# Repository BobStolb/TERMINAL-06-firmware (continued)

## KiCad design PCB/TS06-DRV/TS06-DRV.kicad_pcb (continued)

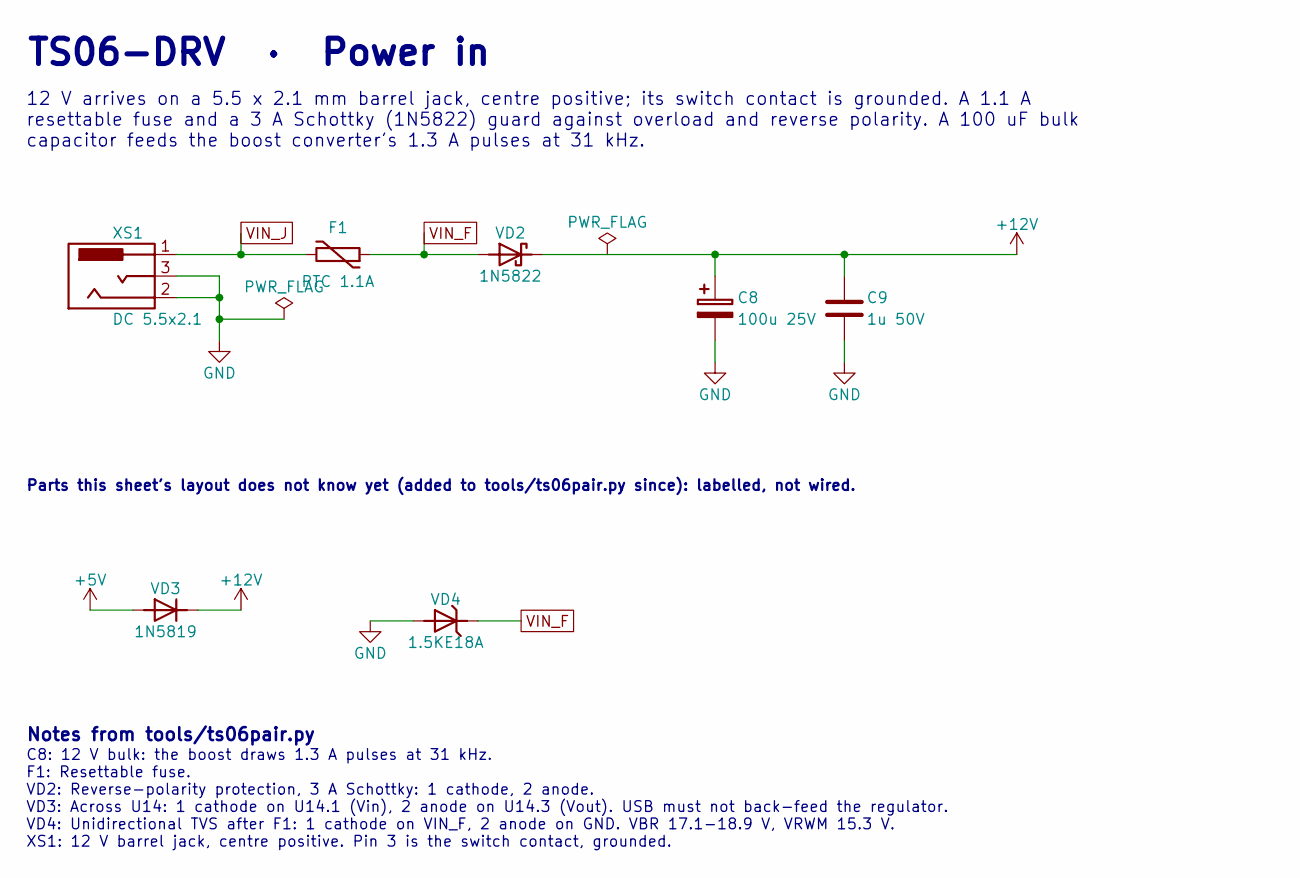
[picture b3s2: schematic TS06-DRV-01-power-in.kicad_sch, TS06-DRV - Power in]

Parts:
C8: 100u 25V; TS06_CP_Radial_D6.3mm_P2.50mm
C9: 1u 50V; TS06_C_Disc_P5.00mm_R270
F1: PTC 1.1A; TS06_Fuse_PTC_MF-RG1100
VD2: 1N5822; TS06_D_DO-201AD_P15.24mm_R180
VD3: 1N5819; TS06_D_DO-41_P10.16mm
VD4: 1.5KE18A; TS06_D_DO-201AD_P15.24mm
XS1: DC 5.5x2.1; TS06_BarrelJack_Horizontal

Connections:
+5V: VD3.2 (A); also elsewhere on the board
+12V: C8.1, C9.1, VD2.1 (K), VD3.1 (K); also elsewhere on the board
GND: C8.2, C9.2, VD4.2 (A), XS1.2 (-), XS1.3 (SW); also elsewhere on the board
VIN_F: F1.2, VD2.2 (A), VD4.1 (K)
VIN_J: F1.1, XS1.1 (+)

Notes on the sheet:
TS06-DRV · Power in
12 V arrives on a 5.5 x 2.1 mm barrel jack, centre positive; its switch contact is grounded. A 1.1 A resettable fuse and a 3 A Schottky (1N5822) guard against overload and reverse polarity. A 100 uF bulk capacitor feeds the boost converter's 1.3 A pulses at 31 kHz.
Parts this sheet's layout does not know yet (added to tools/ts06pair.py since): labelled, not wired.
Notes from tools/ts06pair.py
C8: 12 V bulk: the boost draws 1.3 A pulses at 31 kHz. F1: Resettable fuse. VD2: Reverse-polarity protection, 3 A Schottky: 1 cathode, 2 anode. VD3: Across U14: 1 cathode on U14.1 (Vin), 2 anode on U14.3 (Vout). USB must not back-feed the regulator. VD4: Unidirectional TVS after F1: 1 cathode on VI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

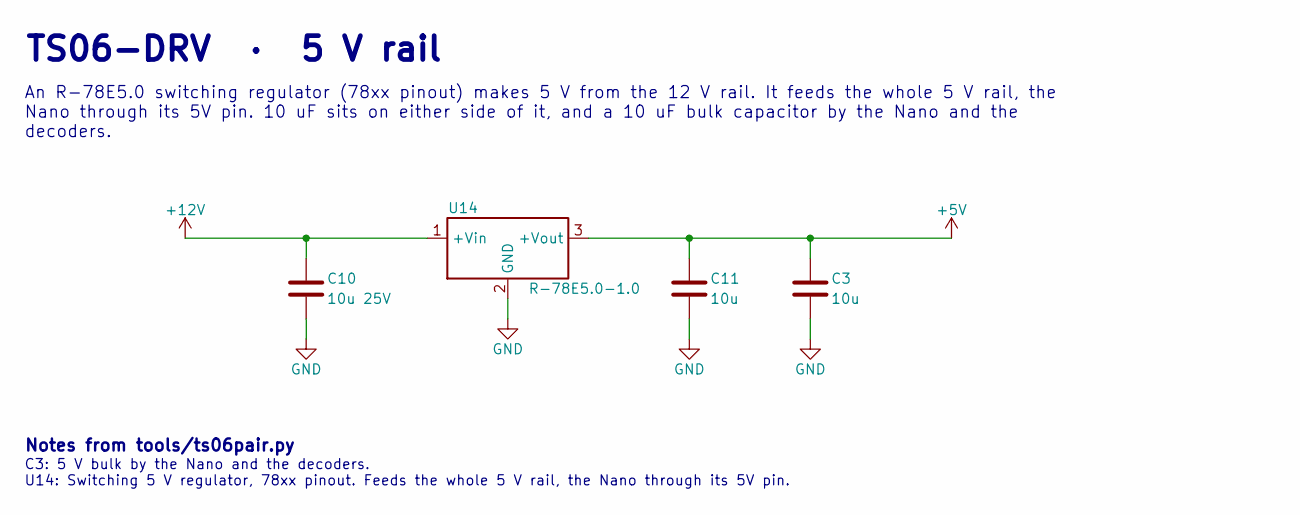
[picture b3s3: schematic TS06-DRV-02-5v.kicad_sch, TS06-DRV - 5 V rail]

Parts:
C3: 10u; TS06_C_Disc_P5.00mm
C10: 10u 25V; TS06_C_Disc_P5.00mm_R270
C11: 10u; TS06_C_Disc_P5.00mm_R90
U14: R-78E5.0-1.0; TS06_R-78E_SIP3

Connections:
+5V: C3.1, C11.1, U14.3 (+Vout); also elsewhere on the board
+12V: C10.1, U14.1 (+Vin); also elsewhere on the board
GND: C3.2, C10.2, C11.2, U14.2 (GND); also elsewhere on the board

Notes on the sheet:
TS06-DRV · 5 V rail
An R-78E5.0 switching regulator (78xx pinout) makes 5 V from the 12 V rail. It feeds the whole 5 V rail, the Nano through its 5V pin. 10 uF sits on either side of it, and a 10 uF bulk capacitor by the Nano and the decoders.
Notes from tools/ts06pair.py
C3: 5 V bulk by the Nano and the decoders. U14: Switching 5 V regulator, 78xx pinout. Feeds the whole 5 V rail, the Nano through its 5V pin.

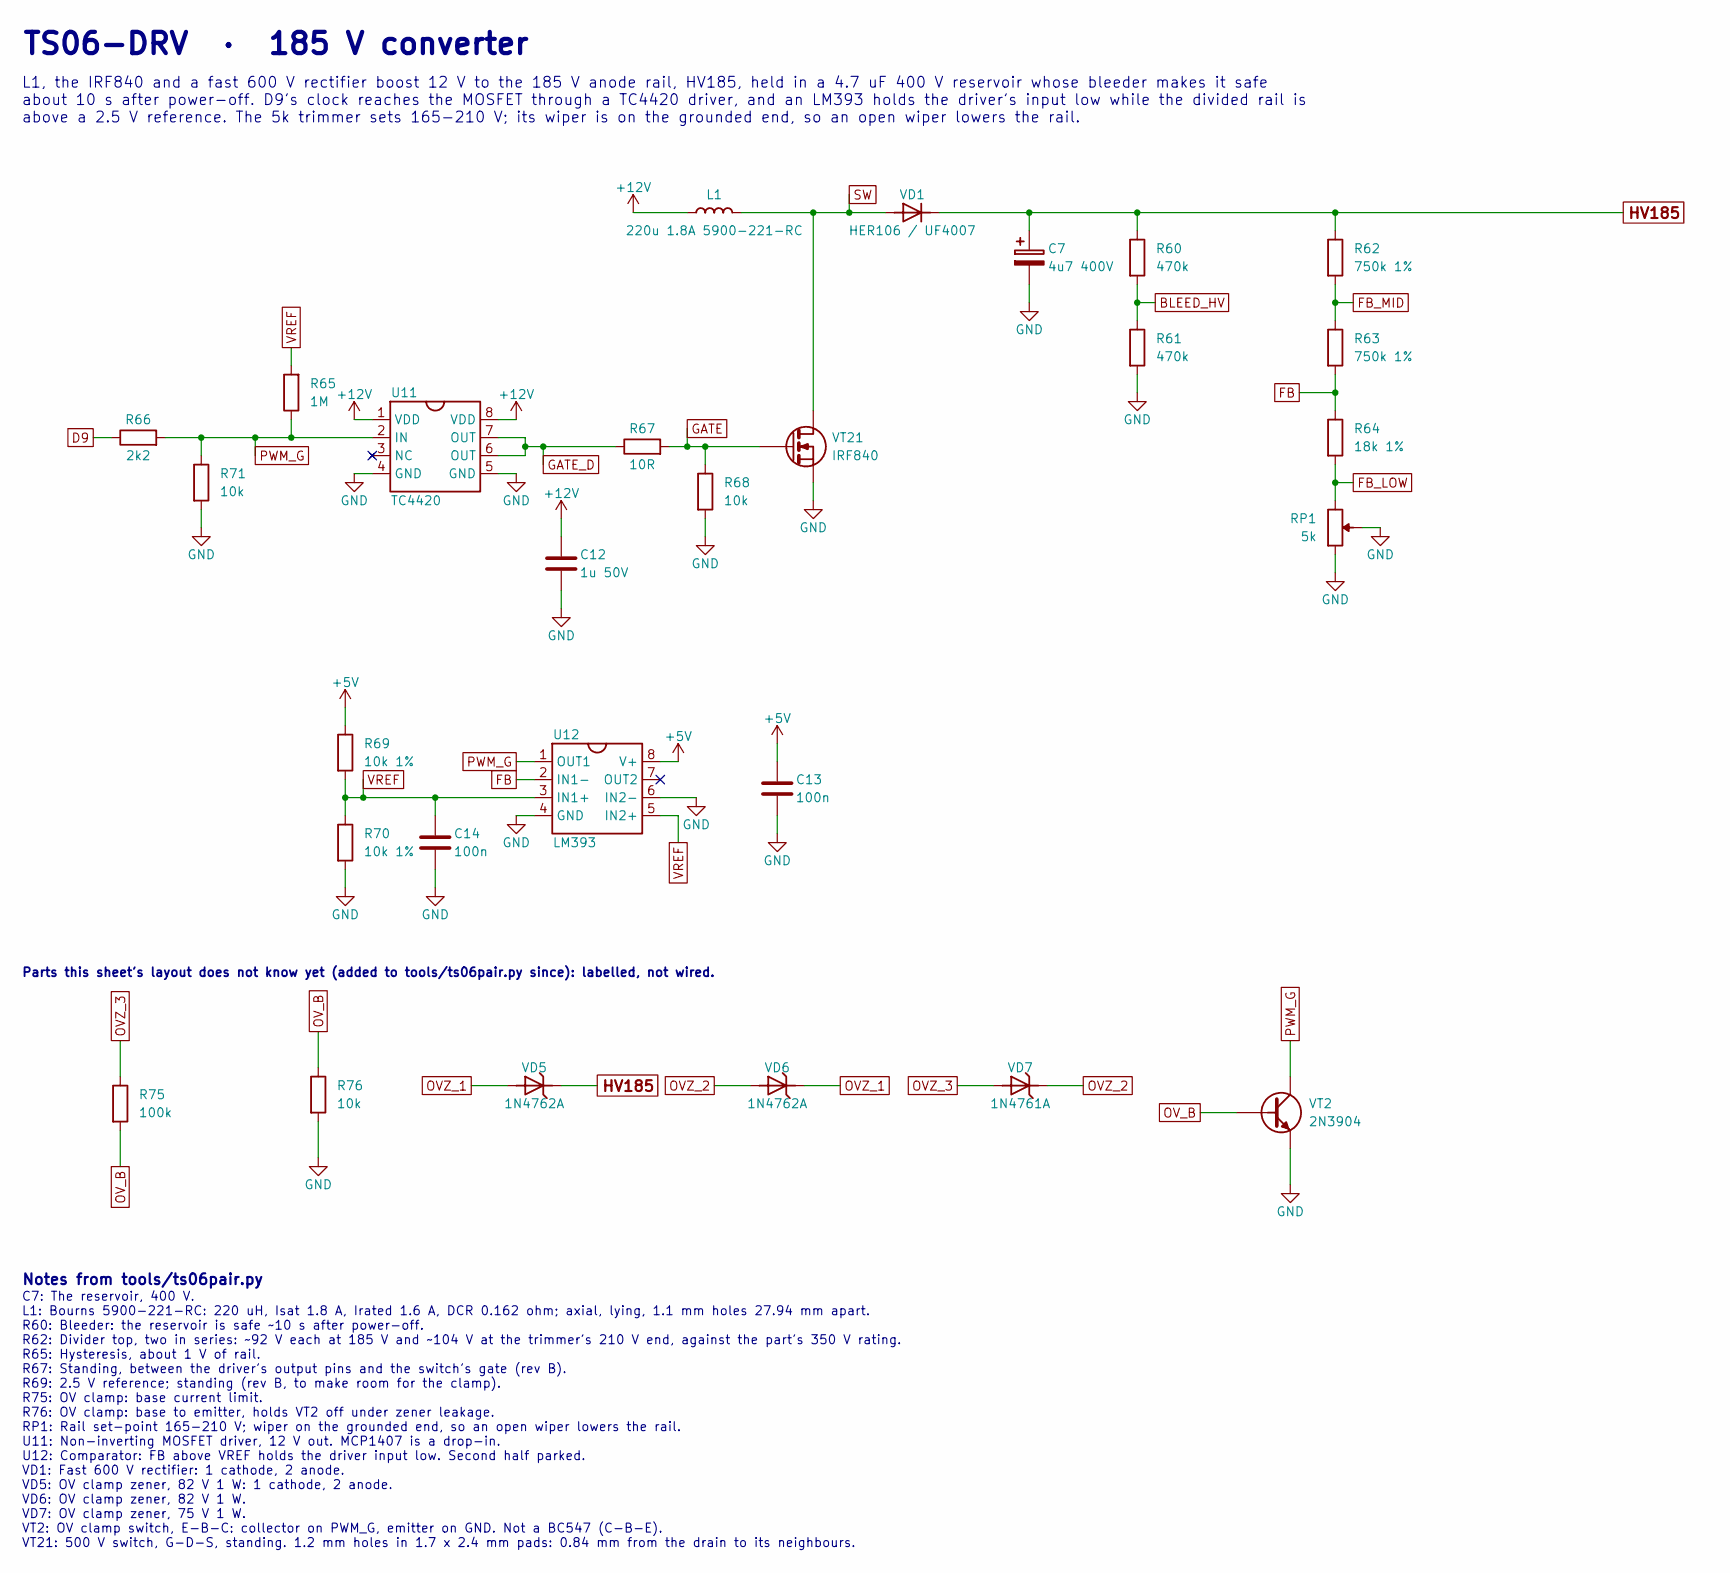
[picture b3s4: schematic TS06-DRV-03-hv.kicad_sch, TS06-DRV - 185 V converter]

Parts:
C7: 4u7 400V; TS06_CP_Radial_D10.0mm_P5.00mm_R180
C12: 1u 50V; TS06_C_Disc_P5.00mm_R270
C13: 100n; TS06_C_Disc_P5.00mm_R180
C14: 100n; TS06_C_Disc_P5.00mm
L1: 220u 1.8A 5900-221-RC; TS06_L_Axial_D11.5mm_L22.9mm_P27.94mm
R60, R61: 470k; TS06_R_Axial_MLT-0.5_P15.24mm
R62: 750k 1%; TS06_R_Axial_MLT-0.5_P15.24mm
R63: 750k 1%; TS06_R_Axial_MLT-0.5_P15.24mm_R270
R64: 18k 1%; TS06_R_Axial_DIN0207_P10.16mm
R65: 1M; TS06_R_Axial_DIN0207_P2.54mm_Vertical_R180
R66: 2k2; TS06_R_Axial_DIN0207_P2.54mm_Vertical_R270
R67: 10R; TS06_R_Axial_DIN0207_P2.54mm_Vertical
R68: 10k; TS06_R_Axial_DIN0207_P2.54mm_Vertical_R90
R69, R70: 10k 1%; TS06_R_Axial_DIN0207_P2.54mm_Vertical_R90
R71: 10k; TS06_R_Axial_DIN0207_P2.54mm_Vertical_R180
R75: 100k; TS06_R_Axial_DIN0207_P10.16mm_R180
R76: 10k; TS06_R_Axial_DIN0207_P10.16mm
RP1: 5k; TS06_Trimmer_3296W
U11: TC4420; TS06_DIP-8_W7.62mm_Socket
U12: LM393; TS06_DIP-8_W7.62mm_Socket_R180
VD1: HER106 / UF4007; TS06_D_DO-41_P10.16mm_R180
VD5: 1N4762A; TS06_D_DO-41_P10.16mm
VD6: 1N4762A; TS06_D_DO-41_P10.16mm_R180
VD7: 1N4761A; TS06_D_DO-41_P10.16mm
VT2: 2N3904; TS06_TO-92_Inline_Wide_R180
VT21: IRF840; TS06_TO-220-3_Vertical_HV

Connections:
+5V: C13.1, R69.1, U12.8 (V+); also elsewhere on the board
+12V: C12.1, L1.1, U11.1 (VDD), U11.8 (VDD); also elsewhere on the board
BLEED_HV: R60.2, R61.1
D9: R66.1; also elsewhere on the board
FB: R63.2, R64.1, U12.2 (IN1-)
FB_LOW: R64.2, RP1.1
FB_MID: R62.2, R63.1
GATE: R67.2, R68.1, VT21.1 (G)
GATE_D: R67.1, U11.6 (OUT), U11.7 (OUT)
GND: C7.2, C12.2, C13.2, C14.2, R61.2, R68.2, R70.2, R71.2, R76.2, RP1.2 (W), RP1.3, U11.4 (GND), U11.5 (GND), U12.4 (GND), U12.6 (IN2-), VT2.1 (E), VT21.3 (S); also elsewhere on the board
HV185: C7.1, R60.1, R62.1, VD1.1 (K), VD5.1 (K); also elsewhere on the board
OVZ_1: VD5.2 (A), VD6.1 (K)
OVZ_2: VD6.2 (A), VD7.1 (K)
OVZ_3: R75.1, VD7.2 (A)
OV_B: R75.2, R76.1, VT2.2 (B)
PWM_G: R65.1, R66.2, R71.1, U11.2 (IN), U12.1 (OUT1), VT2.3 (C)
SW: L1.2, VD1.2 (A), VT21.2 (D)
VREF: C14.1, R65.2, R69.2, R70.1, U12.3 (IN1+), U12.5 (IN2+)

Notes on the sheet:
TS06-DRV · 185 V converter
L1, the IRF840 and a fast 600 V rectifier boost 12 V to the 185 V anode rail, HV185, held in a 4.7 uF 400 V reservoir whose bleeder makes it safe about 10 s after power-off. D9's clock reaches the MOSFET through a TC4420 driver, and an LM393 holds the driver's input low while the divided rail is ab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
Parts this sheet's layout does not know yet (added to tools/ts06pair.py since): labelled, not wired.
Notes from tools/ts06pair.py
C7: The reservoir, 400 V. L1: Bourns 5900-221-RC: 220 uH, Isat 1.8 A, Irated 1.6 A, DCR 0.162 ohm; axial, lying, 1.1 mm holes 27.94 mm apart. R60: Bleeder: the reservoir is safe ~10 s after power-off. R62: Divider top, two in series: ~92 V each at 185 V and ~104 V at the trimmer's 210 V end, agains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

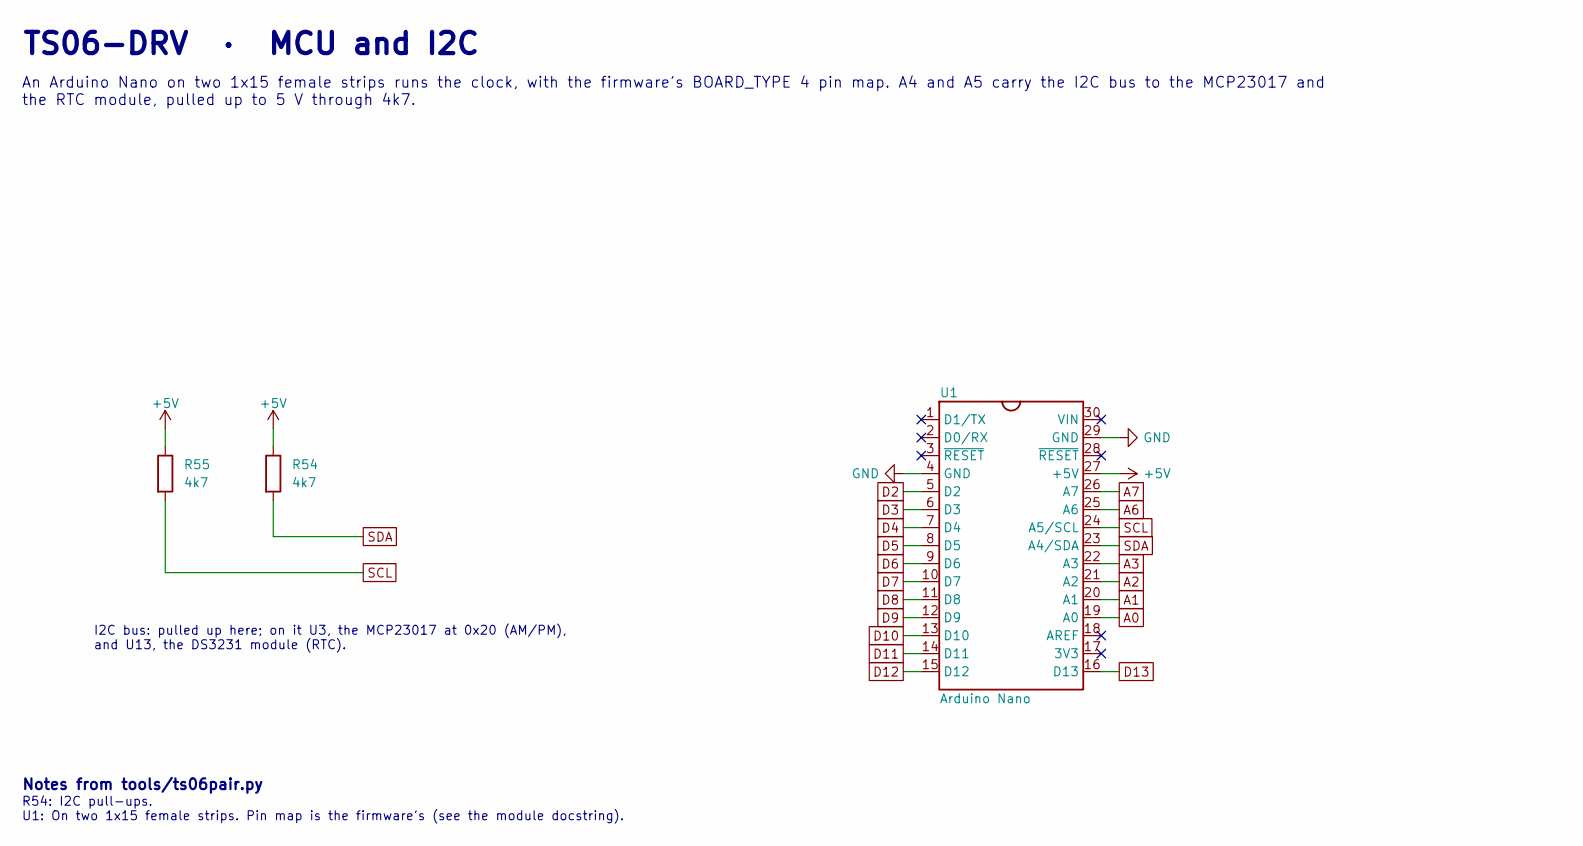
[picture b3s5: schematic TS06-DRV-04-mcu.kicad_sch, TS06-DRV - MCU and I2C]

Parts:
R54, R55: 4k7; TS06_R_Axial_DIN0207_P2.54mm_Vertical
U1: Arduino Nano; TS06_Arduino_Nano_R90

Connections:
+5V: R54.1, R55.1, U1.27 (+5V); also elsewhere on the board
A0: U1.19 (A0); also elsewhere on the board
A1: U1.20 (A1); also elsewhere on the board
A2: U1.21 (A2); also elsewhere on the board
A3: U1.22 (A3); also elsewhere on the board
A6: U1.25 (A6); also elsewhere on the board
A7: U1.26 (A7); also elsewhere on the board
D2: U1.5 (D2); also elsewhere on the board
D3: U1.6 (D3); also elsewhere on the board
D4: U1.7 (D4); also elsewhere on the board
D5: U1.8 (D5); also elsewhere on the board
D6: U1.9 (D6); also elsewhere on the board
D7: U1.10 (D7); also elsewhere on the board
D8: U1.11 (D8); also elsewhere on the board
D9: U1.12 (D9); also elsewhere on the board
D10: U1.13 (D10); also elsewhere on the board
D11: U1.14 (D11); also elsewhere on the board
D12: U1.15 (D12); also elsewhere on the board
D13: U1.16 (D13); also elsewhere on the board
GND: U1.4 (GND), U1.29 (GND); also elsewhere on the board
SCL: R55.2, U1.24 (A5/SCL); also elsewhere on the board
SDA: R54.2, U1.23 (A4/SDA); also elsewhere on the board

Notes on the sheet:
TS06-DRV · MCU and I2C
An Arduino Nano on two 1x15 female strips runs the clock, with the firmware's BOARD_TYPE 4 pin map. A4 and A5 carry the I2C bus to the MCP23017 and the RTC module, pulled up to 5 V through 4k7.
I2C bus: pulled up here; on it U3, the MCP23017 at 0x20 (AM/PM), and U13, the DS3231 module (RTC).
Notes from tools/ts06pair.py
R54: I2C pull-ups. U1: On two 1x15 female strips. Pin map is the firmware's (see the module docstring).

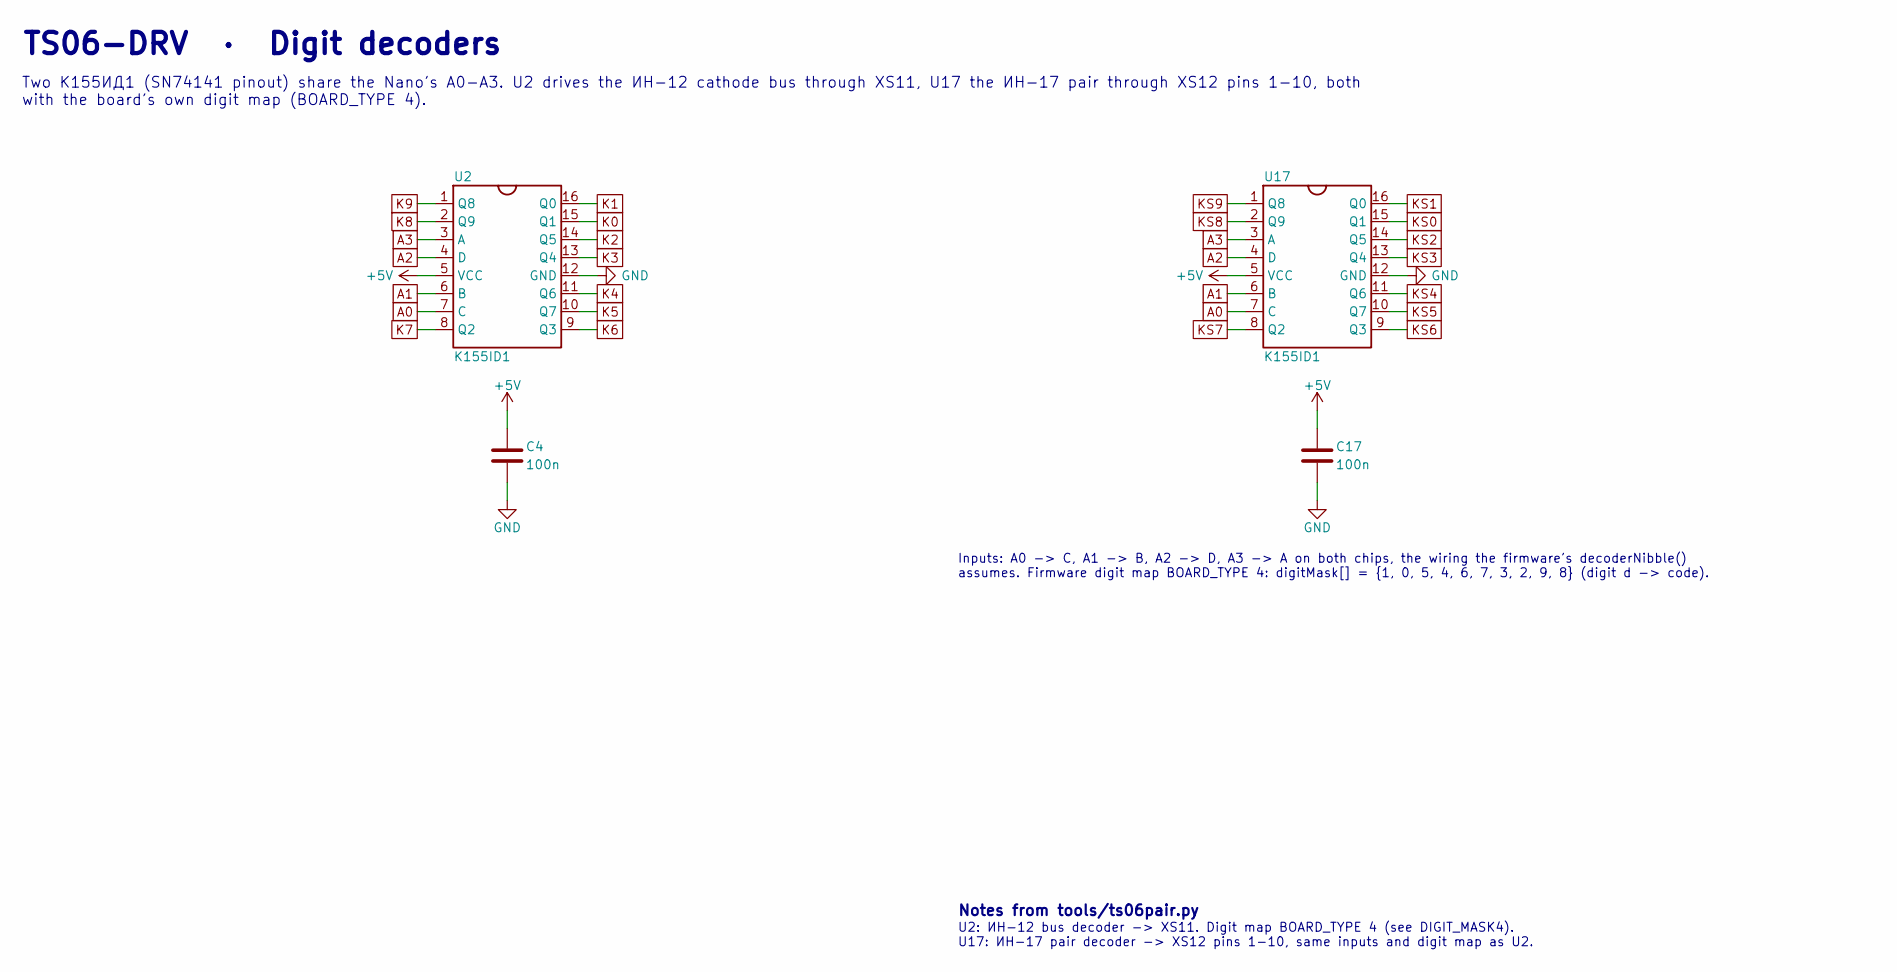
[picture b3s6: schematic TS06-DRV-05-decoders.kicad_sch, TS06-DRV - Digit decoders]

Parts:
C4: 100n; TS06_C_Disc_P5.00mm_R270
C17: 100n; TS06_C_Disc_P5.00mm
U2: K155ID1; TS06_DIP-16_W7.62mm_Socket_Oval_R180
U17: K155ID1; TS06_DIP-16_W7.62mm_Socket_Oval_R90

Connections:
+5V: C4.1, C17.1, U2.5 (VCC), U17.5 (VCC); also elsewhere on the board
A0: U2.7 (C), U17.7 (C); also elsewhere on the board
A1: U2.6 (B), U17.6 (B); also elsewhere on the board
A2: U2.4 (D), U17.4 (D); also elsewhere on the board
A3: U2.3 (A), U17.3 (A); also elsewhere on the board
GND: C4.2, C17.2, U2.12 (GND), U17.12 (GND); also elsewhere on the board
K0: U2.15 (Q1); also elsewhere on the board
K1: U2.16 (Q0); also elsewhere on the board
K2: U2.14 (Q5); also elsewhere on the board
K3: U2.13 (Q4); also elsewhere on the board
K4: U2.11 (Q6); also elsewhere on the board
K5: U2.10 (Q7); also elsewhere on the board
K6: U2.9 (Q3); also elsewhere on the board
K7: U2.8 (Q2); also elsewhere on the board
K8: U2.2 (Q9); also elsewhere on the board
K9: U2.1 (Q8); also elsewhere on the board
KS0: U17.15 (Q1); also elsewhere on the board
KS1: U17.16 (Q0); also elsewhere on the board
KS2: U17.14 (Q5); also elsewhere on the board
KS3: U17.13 (Q4); also elsewhere on the board
KS4: U17.11 (Q6); also elsewhere on the board
KS5: U17.10 (Q7); also elsewhere on the board
KS6: U17.9 (Q3); also elsewhere on the board
KS7: U17.8 (Q2); also elsewhere on the board
KS8: U17.2 (Q9); also elsewhere on the board
KS9: U17.1 (Q8); also elsewhere on the board

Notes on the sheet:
TS06-DRV · Digit decoders
Two К155ИД1 (SN74141 pinout) share the Nano's A0-A3. U2 drives the ИН-12 cathode bus through XS11, U17 the ИН-17 pair through XS12 pins 1-10, both with the board's own digit map (BOARD_TYPE 4).
Inputs: A0 -> C, A1 -> B, A2 -> D, A3 -> A on both chips, the wiring the firmware's decoderNibble() assumes. Firmware digit map BOARD_TYPE 4: digitMask[] = {1, 0, 5, 4, 6, 7, 3, 2, 9, 8} (digit d -> code).
Notes from tools/ts06pair.py
U2: ИН-12 bus decoder -> XS11. Digit map BOARD_TYPE 4 (see DIGIT_MASK4). U17: ИН-17 pair decoder -> XS12 pins 1-10, same inputs and digit map as U2.

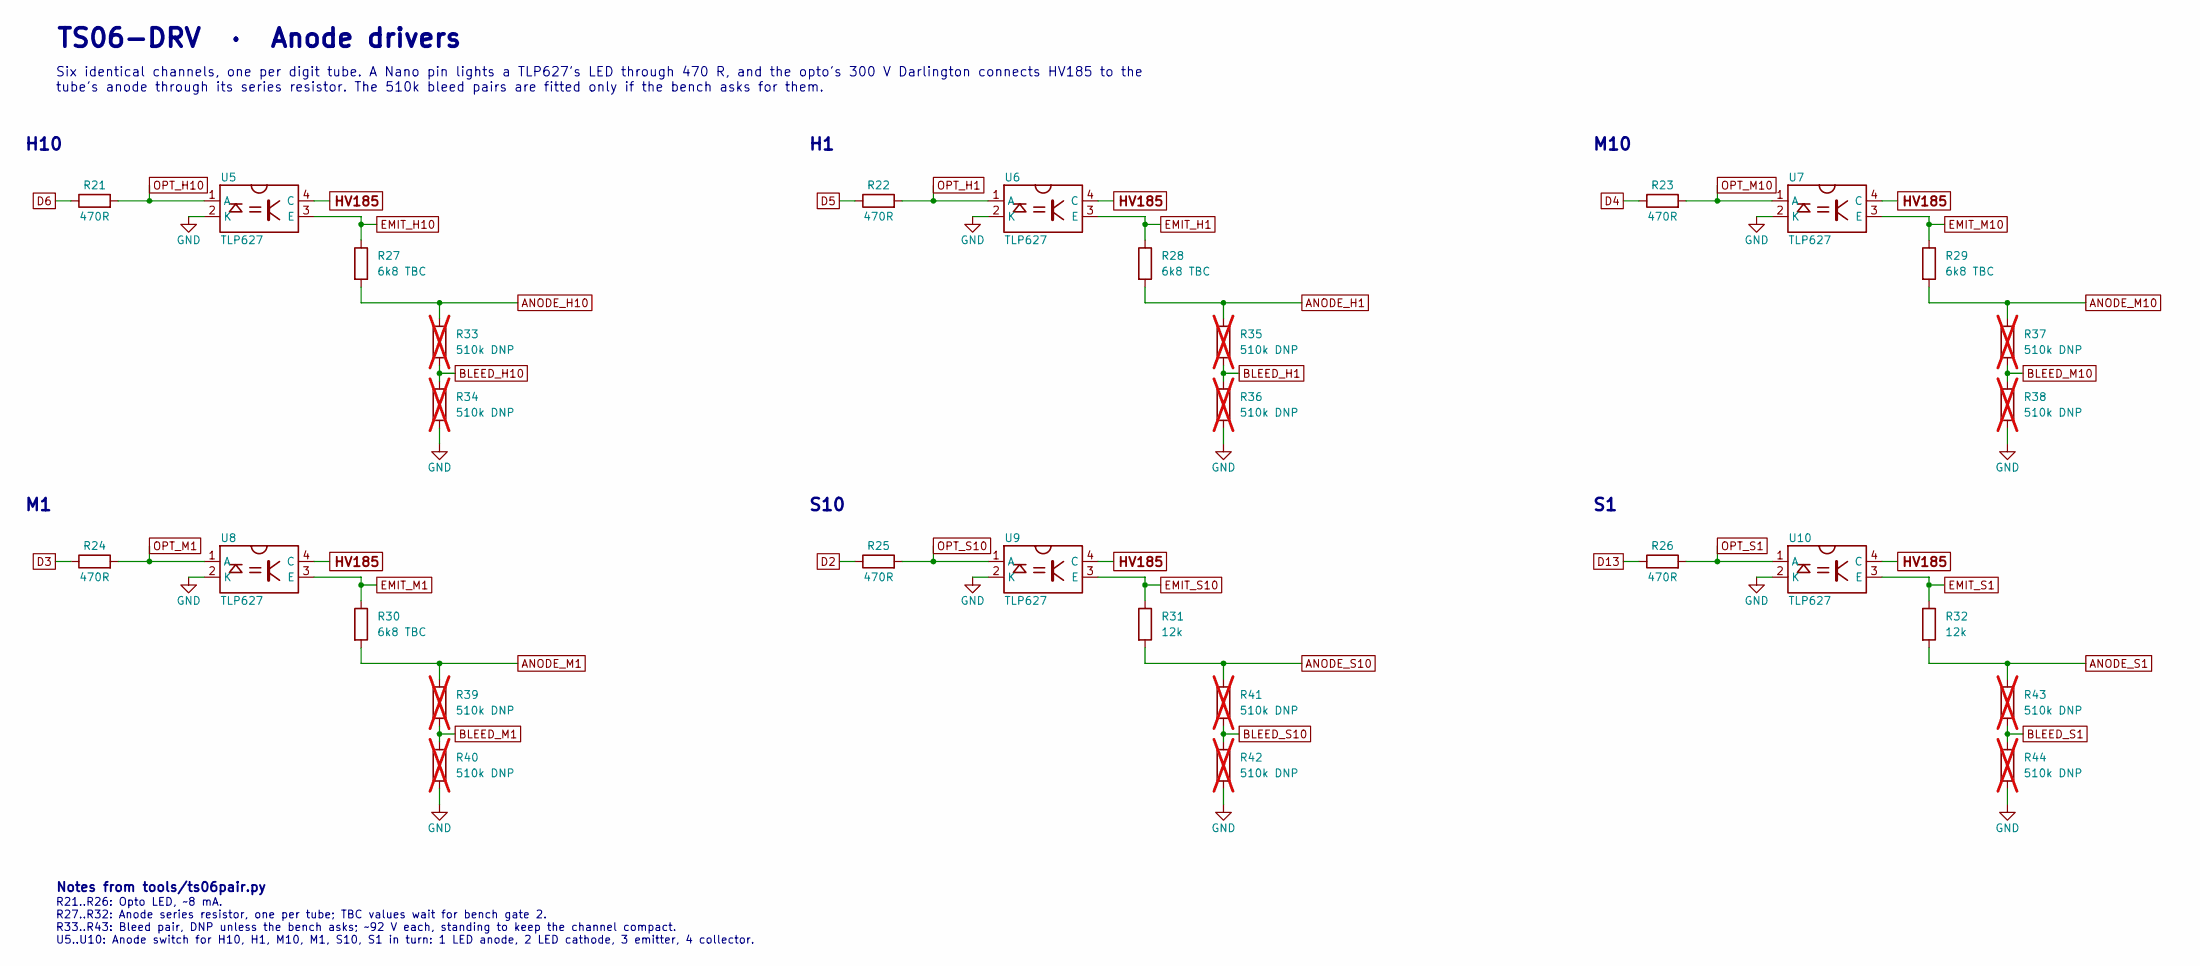
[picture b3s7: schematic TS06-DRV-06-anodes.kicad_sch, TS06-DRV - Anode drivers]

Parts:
R21, R22: 470R; TS06_R_Axial_DIN0207_P10.16mm_R270
R23, R24, R25, R26: 470R; TS06_R_Axial_DIN0207_P2.54mm_Vertical_R270
R27, R28, R29, R30: 6k8 TBC; TS06_R_Axial_MLT-0.5_P15.24mm
R31: 12k; TS06_R_Axial_MLT-0.5_P15.24mm_R180
R32: 12k; TS06_R_Axial_MLT-0.5_P15.24mm
R33, R36: 510k DNP; TS06_R_Axial_DIN0207_P2.54mm_Vertical_R180; not fitted
R34, R35, R37, R38, R39, R40, R42: 510k DNP; TS06_R_Axial_DIN0207_P2.54mm_Vertical; not fitted
R41, R43, R44: 510k DNP; TS06_R_Axial_DIN0207_P2.54mm_Vertical_R90; not fitted
U5, U6, U7, U8, U9, U10: TLP627; TS06_DIP-4_W7.62mm_Socket_R270

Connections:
ANODE_H1: R28.2, R35.1; also elsewhere on the board
ANODE_H10: R27.2, R33.1; also elsewhere on the board
ANODE_M1: R30.2, R39.1; also elsewhere on the board
ANODE_M10: R29.2, R37.1; also elsewhere on the board
ANODE_S1: R32.2, R43.1; also elsewhere on the board
ANODE_S10: R31.2, R41.1; also elsewhere on the board
BLEED_H1: R35.2, R36.1
BLEED_H10: R33.2, R34.1
BLEED_M1: R39.2, R40.1
BLEED_M10: R37.2, R38.1
BLEED_S1: R43.2, R44.1
BLEED_S10: R41.2, R42.1
D2: R25.1; also elsewhere on the board
D3: R24.1; also elsewhere on the board
D4: R23.1; also elsewhere on the board
D5: R22.1; also elsewhere on the board
D6: R21.1; also elsewhere on the board
D13: R26.1; also elsewhere on the board
EMIT_H1: R28.1, U6.3 (E)
EMIT_H10: R27.1, U5.3 (E)
EMIT_M1: R30.1, U8.3 (E)
EMIT_M10: R29.1, U7.3 (E)
EMIT_S1: R32.1, U10.3 (E)
EMIT_S10: R31.1, U9.3 (E)
GND: R34.2, R36.2, R38.2, R40.2, R42.2, R44.2, U5.2 (K), U6.2 (K), U7.2 (K), U8.2 (K), U9.2 (K), U10.2 (K); also elsewhere on the board
HV185: U5.4 (C), U6.4 (C), U7.4 (C), U8.4 (C), U9.4 (C), U10.4 (C); also elsewhere on the board
OPT_H1: R22.2, U6.1 (A)
OPT_H10: R21.2, U5.1 (A)
OPT_M1: R24.2, U8.1 (A)
OPT_M10: R23.2, U7.1 (A)
OPT_S1: R26.2, U10.1 (A)
OPT_S10: R25.2, U9.1 (A)

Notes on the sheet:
TS06-DRV · Anode drivers
Six identical channels, one per digit tube. A Nano pin lights a TLP627's LED through 470 R, and the opto's 300 V Darlington connects HV185 to the tube's anode through its series resistor. The 510k bleed pairs are fitted only if the bench asks for them.
H10
M10
S10
Notes from tools/ts06pair.py
R21..R26: Opto LED, ~8 mA. R27..R32: Anode series resistor, one per tube; TBC values wait for bench gate 2. R33..R43: Bleed pair, DNP unless the bench asks; ~92 V each, standing to keep the channel compact. U5..U10: Anode switch for H10, H1, M10, M1, S10, S1 in turn: 1 LED anode, 2 LED cathode, 3 e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

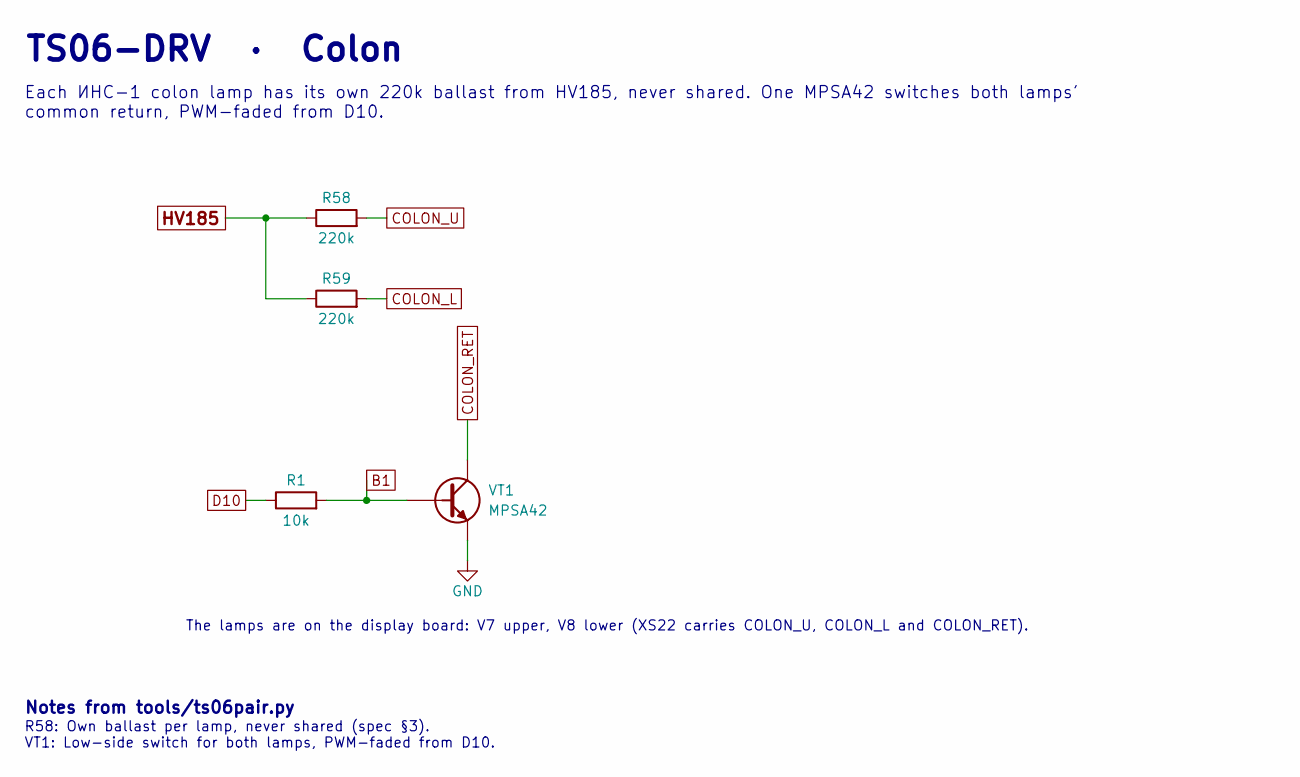
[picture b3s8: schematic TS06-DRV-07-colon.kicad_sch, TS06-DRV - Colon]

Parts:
R1: 10k; TS06_R_Axial_DIN0207_P2.54mm_Vertical_R270
R58, R59: 220k; TS06_R_Axial_MLT-0.5_P15.24mm_R270
VT1: MPSA42; TS06_TO-92_Inline_Wide_R270

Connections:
B1: R1.2, VT1.2 (B)
COLON_L: R59.2; also elsewhere on the board
COLON_RET: VT1.3 (C); also elsewhere on the board
COLON_U: R58.2; also elsewhere on the board
D10: R1.1; also elsewhere on the board
GND: VT1.1 (E); also elsewhere on the board
HV185: R58.1, R59.1; also elsewhere on the board

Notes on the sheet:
TS06-DRV · Colon
Each ИНС-1 colon lamp has its own 220k ballast from HV185, never shared. One MPSA42 switches both lamps' common return, PWM-faded from D10.
The lamps are on the display board: V7 upper, V8 lower (XS22 carries COLON_U, COLON_L and COLON_RET).
Notes from tools/ts06pair.py
R58: Own ballast per lamp, never shared (spec §3). VT1: Low-side switch for both lamps, PWM-faded from D10.

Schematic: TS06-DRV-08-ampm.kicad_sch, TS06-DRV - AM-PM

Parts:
C1: 100n; TS06_C_Disc_P5.00mm_R180
C15, C16: 100n; TS06_C_Disc_P5.00mm
R56, R57: 18k; TS06_R_Axial_MLT-0.5_P15.24mm
U3: MCP23017-E/SP; TS06_DIP-28_W7.62mm_Socket_R270
U15, U16: K155ID1; TS06_DIP-16_W7.62mm_Socket_Oval_R90

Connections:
+5V: C1.1, C15.1, C16.1, U3.9 (VDD), U3.18 (~RESET), U15.5 (VCC), U16.5 (VCC); also elsewhere on the board
ANODE_AM: R56.1; also elsewhere on the board
ANODE_PM: R57.1; also elsewhere on the board
CAT_A_KILO: U16.11 (Q6); also elsewhere on the board
CAT_A_MEGA: U16.13 (Q4); also elsewhere on the board
CAT_A_MICRO: U16.2 (Q9); also elsewhere on the board
CAT_A_MILLI: U16.14 (Q5); also elsewhere on the board
CAT_A_MINUS: U16.16 (Q0); also elsewhere on the board
CAT_A_NANO: U16.8 (Q2); also elsewhere on the board
CAT_A_P: U16.1 (Q8); also elsewhere on the board
CAT_A_PCT: U16.9 (Q3); also elsewhere on the board
CAT_A_PI: U16.10 (Q7); also elsewhere on the board
CAT_A_PLUS: U16.15 (Q1); also elsewhere on the board
CAT_B_AMP: U15.8 (Q2); also elsewhere on the board
CAT_B_FARAD: U15.15 (Q1); also elsewhere on the board
CAT_B_HENRY: U15.13 (Q4); also elsewhere on the board
CAT_B_HERTZ: U15.14 (Q5); also elsewhere on the board
CAT_B_OHM: U15.9 (Q3); also elsewhere on the board
CAT_B_SIEMENS: U15.10 (Q7); also elsewhere on the board
CAT_B_VOLT: U15.11 (Q6); also elsewhere on the board
CAT_B_WATT: U15.16 (Q0); also elsewhere on the board
GND: C1.2, C15.2, C16.2, U3.10 (VSS), U3.15 (A0), U3.16 (A1), U3.17 (A2), U15.12 (GND), U16.12 (GND); also elsewhere on the board
HV185: R56.2, R57.2; also elsewhere on the board
SCL: U3.12 (SCL); also elsewhere on the board
SDA: U3.13 (SDA); also elsewhere on the board
XA0: U3.21 (GPA0), U15.7 (C)
XA1: U3.22 (GPA1), U15.6 (B)
XA2: U3.23 (GPA2), U15.4 (D)
XA3: U3.24 (GPA3), U15.3 (A)
XA4: U3.25 (GPA4), U16.7 (C)
XA5: U3.26 (GPA5), U16.6 (B)
XA6: U3.27 (GPA6), U16.4 (D)
XA7: U3.28 (GPA7), U16.3 (A)
XB0: U3.1 (GPB0); also elsewhere on the board
XB1: U3.2 (GPB1); also elsewhere on the board
XB2: U3.3 (GPB2); also elsewhere on the board
XB3: U3.4 (GPB3); also elsewhere on the board
XB4: U3.5 (GPB4); also elsewhere on the board
XB5: U3.6 (GPB5); also elsewhere on the board
XB6: U3.7 (GPB6); also elsewhere on the board
XB7: U3.8 (GPB7); also elsewhere on the board

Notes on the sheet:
TS06-DRV · AM-PM
One MCP23017 at I2C address 0x20 drives two К155ИД1: GPA3..0 pick the ИН-15Б glyph and GPA7..4 the ИН-15А glyph; codes 10-15 blank a tube. Each ИН-15 is lit continuously through an 18k anode resistor, about 2.5 mA. The expander's port B drives the backlight LEDs.
Codes 10-15 light nothing: the tube is blank. The firmware keeps the inverse of this table.
Notes from tools/ts06pair.py
R56: Static anode resistor, ИН-15Б (bench gate 2 checks it). R57: Static anode resistor, ИН-15А. U3: I2C expander at 0x20 (A0-A2 grounded), 300-mil SPDIP. GPA3..0 -> U15 (ИН-15Б), GPA7..4 -> U16 (ИН-15А), GPB0-7 -> backlight LEDs through RN1. U15: ИН-15Б decoder, nibble on GPA3..0 per XA_IN. Codes 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

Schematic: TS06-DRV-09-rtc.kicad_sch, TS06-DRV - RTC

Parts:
U13: DS3231 mini; TS06_PinHeader_1x05_DS3231_R270

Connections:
+5V: U13.5 (+); also elsewhere on the board
GND: U13.1 (-); also elsewhere on the board
SCL: U13.3 (C/SCL); also elsewhere on the board
SDA: U13.4 (D/SDA); also elsewhere on the board

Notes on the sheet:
TS06-DRV · RTC
The small DS3231 module plugs into a 5-way socket, pin order - NC C D + as the stock board's RTC MINI header. It shares the I2C bus with the expander.
Notes from tools/ts06pair.py
U13: A male PLS-5 on the board: the module's own female header plugs onto it and the module lies over it. Pad 1 (square) is GND (-), then NC, C (SCL), D (SDA); the module's pin 1, +, lands on pad 5.

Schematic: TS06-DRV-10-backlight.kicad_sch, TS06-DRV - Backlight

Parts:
R20: 470R; TS06_R_Axial_DIN0207_P2.54mm_Vertical_R270
R53: 220R; TS06_R_Axial_DIN0207_P2.54mm_Vertical_R270
RN1: 8x220R isolated DIP-16; TS06_DIP-16_W7.62mm_Socket_R90
VT20: MPSA42; TS06_TO-92_Inline_Wide_R270

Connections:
B20: R20.2, VT20.2 (B)
BL_A1: RN1.9; also elsewhere on the board
BL_A2: RN1.10; also elsewhere on the board
BL_A3: RN1.11; also elsewhere on the board
BL_A4: RN1.12; also elsewhere on the board
BL_A5: RN1.13; also elsewhere on the board
BL_A6: RN1.14; also elsewhere on the board
BL_A7: RN1.15; also elsewhere on the board
BL_A8: RN1.16; also elsewhere on the board
BL_K: VT20.3 (C); also elsewhere on the board
D11: R20.1; also elsewhere on the board
D12: R53.1; also elsewhere on the board
GND: VT20.1 (E); also elsewhere on the board
M_A: R53.2; also elsewhere on the board
XB0: RN1.8; also elsewhere on the board
XB1: RN1.7; also elsewhere on the board
XB2: RN1.6; also elsewhere on the board
XB3: RN1.5; also elsewhere on the board
XB4: RN1.4; also elsewhere on the board
XB5: RN1.3; also elsewhere on the board
XB6: RN1.2; also elsewhere on the board
XB7: RN1.1; also elsewhere on the board

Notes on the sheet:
TS06-DRV · Backlight
Eight amber LEDs behind the tubes are each sourced from their own MCP23017 port-B pin through an isolated 8 x 220R network; the 'm' LED of AM/PM runs from D12 through 220R. All nine cathodes share BL_K behind one MPSA42, so D11's PWM sets the brightness of them all.
On the display board: BL_A1..BL_A8 feed the anodes of HL1..HL8, M_A the anode of HL9 (the 'm'), and BL_K is all nine cathodes. GPBk of U3 lights HL(k+1): tools/ts06pair.py BL_OF_GPB.
Notes from tools/ts06pair.py
R53: The m LED, from D12. Standing: one of the four series resistors where the Nano's corridor lines end and change face (tools/mkpcb_drv.py). RN1: Isolated resistor network, 8 x 220R (4116R-1-221 class): GPBk -> pin 8-k, resistor to pin 9+k -> its LED. VT20: Common-cathode switch for all nine LEDs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

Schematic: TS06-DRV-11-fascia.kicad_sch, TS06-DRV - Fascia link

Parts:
C5, C6: 100n; TS06_C_Disc_P2.50mm_R180
C18, C19: 10n; TS06_C_Disc_P2.50mm_R270
J1: PH 6 vertical; TS06_JST_PH_B6B-PH-K_Vertical
R72: 1M; TS06_R_Axial_DIN0207_P10.16mm_R180
R73, R74: 1k; TS06_R_Axial_DIN0207_P10.16mm_R180

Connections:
+5V: J1.1; also elsewhere on the board
A6: C5.1, J1.3, R72.1; also elsewhere on the board
A7: C6.1, J1.4; also elsewhere on the board
D7: R73.1; also elsewhere on the board
D7_J: C18.1, J1.5, R73.2
D8: R74.1; also elsewhere on the board
D8_J: C19.1, J1.6, R74.2
GND: C5.2, C6.2, C18.2, C19.2, J1.2, R72.2; also elsewhere on the board

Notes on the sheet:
TS06-DRV · Fascia link
The panel cable leaves on a top-entry 6-way JST PH: +5V, GND, A6, A7, D7, D8, the pin order both fascia builds share. The 100 nF ladder filters on A6 and A7 sit at this end of the cable.
To the fascia: JST PH, 6 ways, top entry.
Parts this sheet's layout does not know yet (added to tools/ts06pair.py since): labelled, not wired.
Notes from tools/ts06pair.py
C5: Ladder filters at the board end (spec §2). C18: Near J1, on the cable side of R73. J1: The panel cable; pin order is the specification both fascia builds share. Top entry, so the cable leaves towards the fascia. R72: A6 pull-down: a defined 0 with the fascia unplugged. R73: Series resistor on t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
